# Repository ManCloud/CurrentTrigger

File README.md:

# CurrentTrigger

## Description
This circuit will detect a current flowing through a current mirror and outputting a low-level signal once it reaces a certain threshold.
This is intended to work as a controller detection circuit for various consoles in combination with [DarthCloud](https://github.com/darthcloud)s [BlueRetro](https://github.com/darthcloud/BlueRetro) adapters for internal installation.

## Idle Currents per Console

| Controller | Idle Current |
|-|-|
| N64 (OEM) | 6 mA |
| DS2 (OEM) | 8 mA |
| GC (OEM) | 7.5 mA|
| MegaDrive (OEM)| <1 µA|
| NES (OEM) | <1 µA |

The circuit is designed to reliably output a low-level at a threshold of 300µA! Any controller consuming less in idle state is not detectable.

## Exampe Installation Points

- To be written

## Implemenatations using this approach
GameCube BlueRetro Internal Adapter by Collingall/Laser Bear Industries [Link](https://www.laserbear.net/products/gamecube-blue-retro-internal-adapter)

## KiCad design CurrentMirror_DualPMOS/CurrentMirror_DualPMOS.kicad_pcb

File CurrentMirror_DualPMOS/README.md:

# CurrentTrigger - DualPMOS

## Pinout
J1.1 => VCC
J1.2 => Controller Supply

J2.1 => Controller Sense
J2.2 => GND

## Preview

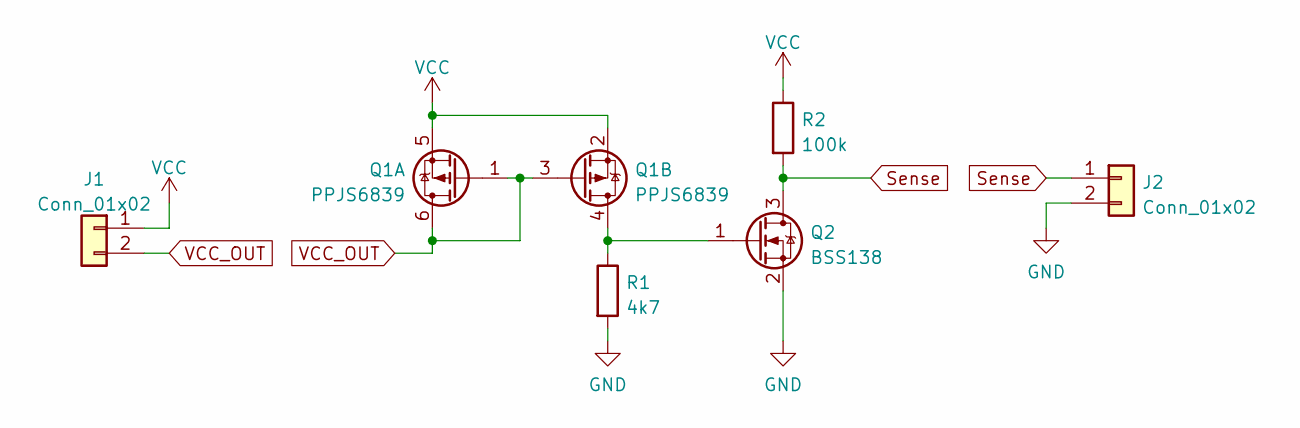
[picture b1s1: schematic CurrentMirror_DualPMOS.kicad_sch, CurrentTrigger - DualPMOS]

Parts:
J1, J2: Conn_01x02; PinHeader_1x02_P2.54mm_Vertical
Q1: PPJS6839; SOT-23-6_Handsoldering
Q2: BSS138; TSOT-23_HandSoldering
R1: 4k7; R_0805_2012Metric_Pad1.20x1.40mm_HandSolder
R2: 100k; R_0805_2012Metric_Pad1.20x1.40mm_HandSolder

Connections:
GND: J2.2, Q2.2 (S), R1.2
unnamed: Q1.4 (D), Q2.1 (G), R1.1
Sense: J2.1, Q2.3 (D), R2.2
VCC: J1.1, Q1.2 (S), Q1.5 (S), R2.1
VCC_OUT: J1.2, Q1.1 (G), Q1.3 (G), Q1.6 (D)

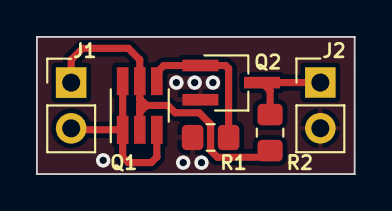
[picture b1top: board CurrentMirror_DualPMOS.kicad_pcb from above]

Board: 2 copper layers, 17.7 x 7.6 mm, 6 parts (0 on the bottom side), 5 nets.

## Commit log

2023-10-30 Fixed GND vias
